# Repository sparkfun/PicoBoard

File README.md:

Picoboard
=========

[ 
*PicoBoard (WIG-10311)*](https://www.sparkfun.com/products/10311)

The PicoBoard allows you to interface hardware sensors with the Scratch programming language.

Repository Contents
-------------------
* **/hardware** - All Eagle design files (.brd, .sch, .STL)
* **/firmware** - PicoBoard source code for an ATmega328.

License Information
-------------------
The contents released under [Creative Commons Share-alike 3.0](http://creativecommons.org/licenses/by-sa/3.0/).

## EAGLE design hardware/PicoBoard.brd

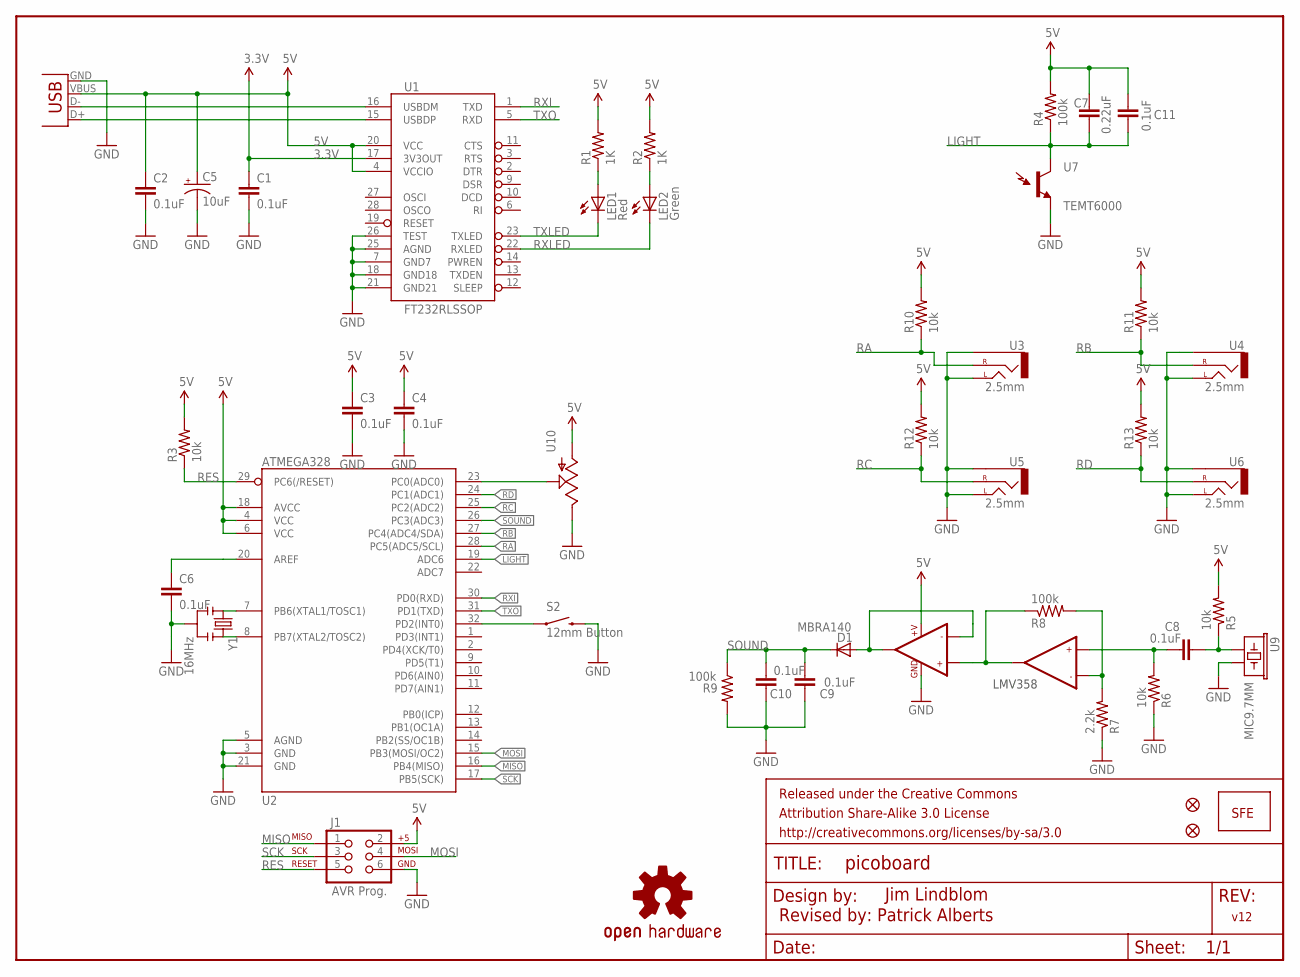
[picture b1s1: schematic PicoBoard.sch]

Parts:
C1, C2, C3, C4, C6, C8, C9, C10, C11: 0.1uF; 0603-CAP
C5: 10uF; EIA3216
C7: 0.22uF; 0603-CAP
D1: MBRA140; SMA-DIODE
FID1, FID2: FIDUCIAL1X2; FIDUCIAL-1X2
FRAME1: FRAME-LETTER; CREATIVE_COMMONS
J1: AVR Prog.; 2X3
JP1: LOGO-SFENEW; SFE-NEW-WEBLOGO
LED1: Red; LED-0603
LED2: Green; LED-0603
LOGO1: OSHW-LOGOL; OSHW-LOGO-L
R1, R2: 1K; 0603-RES
R3, R5, R6, R10, R11, R12, R13: 10k; 0603-RES
R4, R8, R9: 100k; 0603-RES
R7: 2.2k; 0603-RES
S2: 12mm Button; TACTILE-SMD-12MM
U1: FT232RLSSOP; SSOP28DB
U2: ATMEGA328; TQFP32-08
U3, U4, U5, U6: 2.5mm; STEREOJACK2.5MM
U7: TEMT6000; TEMT6000-SEN
U8: LMV358; SO08
U9: MIC9.7MM; MIC-9.7MM
U10: SLIDER60MM; SLIDER
X1: USBSMD; USB-MINIB
Y1: 16MHz; RESONATOR-SMD

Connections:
3.3V: C1.1, U1.17 (3V3OUT)
5V: C2.1, C3.1, C4.1, C5.A (+), C7.1, C11.1, J1.2, R1.2, R2.2, R3.2, R4.2, R5.2, R10.2, R11.2, R12.2, R13.2, U1.4 (VCCIO), U1.20 (VCC), U2.4 (VCC), U2.6 (VCC), U2.18 (AVCC), U8.8 (+V), U10.3 (A), X1.VBUS
GND: C1.2, C2.2, C3.2, C4.2, C5.C (-), C6.2, C9.1, C10.1, J1.6, R6.1, R7.1, R9.2, S2.3 (2), U1.7 (GND7), U1.18 (GND18), U1.21 (GND21), U1.25 (AGND), U1.26 (TEST), U2.3 (GND), U2.5 (AGND), U2.21 (GND), U3.1 (LEFT), U3.5 (SLEEVE), U4.1 (LEFT), U4.5 (SLEEVE), U5.1 (LEFT), U5.5 (SLEEVE), U6.1 (LEFT), U6.5 (SLEEVE), U7.EMITTER (E1), U8.4 (GND), U9.2, U10.1 (E), X1.GND, Y1.2
LIGHT: C7.2, C11.2, R4.1, U2.19 (ADC6), U7.COLLECTOR (C1)
MISO: J1.1, U2.16 (PB4(MISO))
MOSI: J1.4, U2.15 (PB3(MOSI/OC2))
unnamed: LED1.A, R1.1
unnamed: LED2.A, R2.1
unnamed: R7.2, R8.2, U8.6 (-IN2)
unnamed: U2.7 (PB6(XTAL1/TOSC1)), Y1.1
unnamed: U2.8 (PB7(XTAL2/TOSC2)), Y1.3
unnamed: C6.1, U2.20 (AREF)
unnamed: S2.1, U2.32 (PD2(INT0))
unnamed: C8.1, R5.1, U9.1
unnamed: U2.23 (PC0(ADC0)), U10.2A (S)
unnamed: C8.2, R6.2, U8.5 (+IN2)
unnamed: D1.A, U8.1 (OUT1), U8.2 (-IN1)
unnamed: R8.1, U8.3 (+IN1), U8.7 (OUT2)
RA: R10.1, U2.28 (PC5(ADC5/SCL)), U3.4 (RIGHT)
RB: R11.1, U2.27 (PC4(ADC4/SDA)), U4.4 (RIGHT)
RC: R12.1, U2.25 (PC2(ADC2)), U5.4 (RIGHT)
RD: R13.1, U2.24 (PC1(ADC1)), U6.4 (RIGHT)
RES: J1.5, R3.1, U2.29 (PC6(/RESET))
RXI: U1.1 (TXD), U2.30 (PD0(RXD))
RXLED: LED2.C, U1.22 (RXLED)
SCK: J1.3, U2.17 (PB5(SCK))
SOUND: C9.2, C10.2, D1.C, R9.1, U2.26 (PC3(ADC3))
TXLED: LED1.C, U1.23 (TXLED)
TXO: U1.5 (RXD), U2.31 (PD1(TXD))
USB_D+: U1.15 (USBDP), X1.D+
USB_D-: U1.16 (USBDM), X1.D-

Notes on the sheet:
LMV358
Jim Lindblom
Revised by: Patrick Alberts
v12

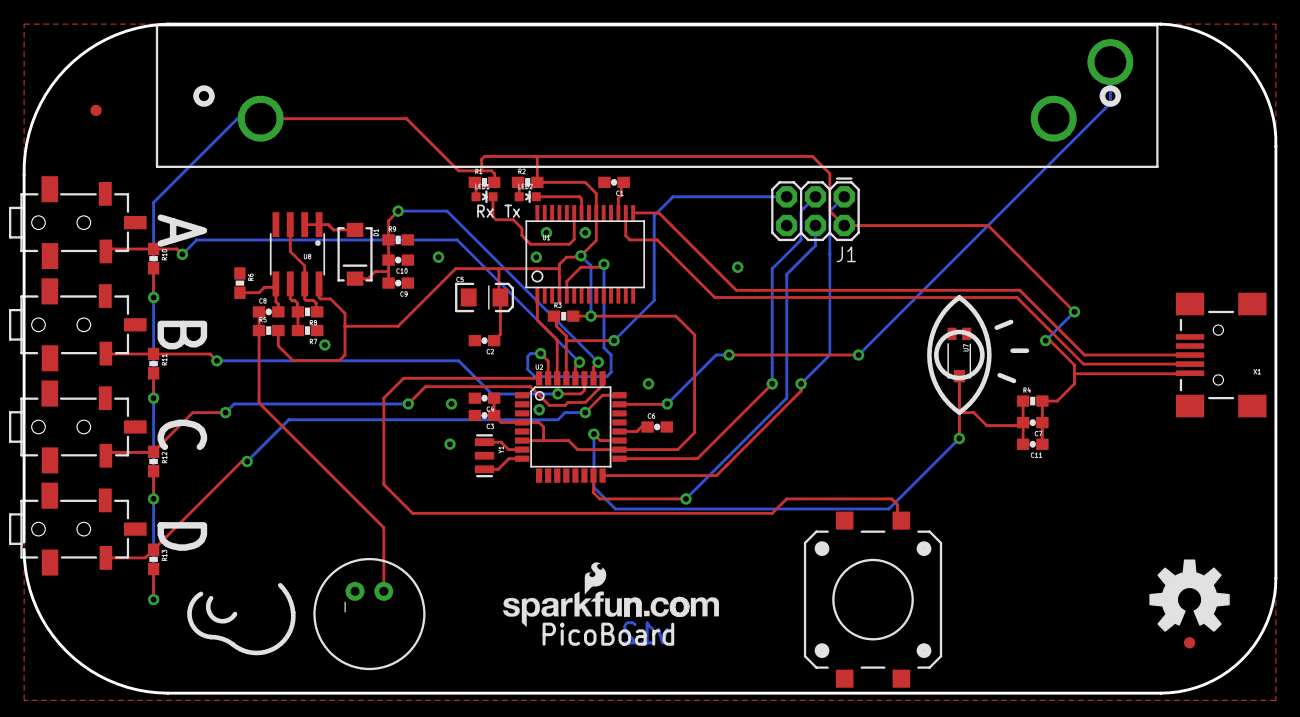
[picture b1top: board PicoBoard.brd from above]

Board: 2 copper layers, 110.5 x 59.1 mm, 46 parts (0 on the bottom side), 31 nets.

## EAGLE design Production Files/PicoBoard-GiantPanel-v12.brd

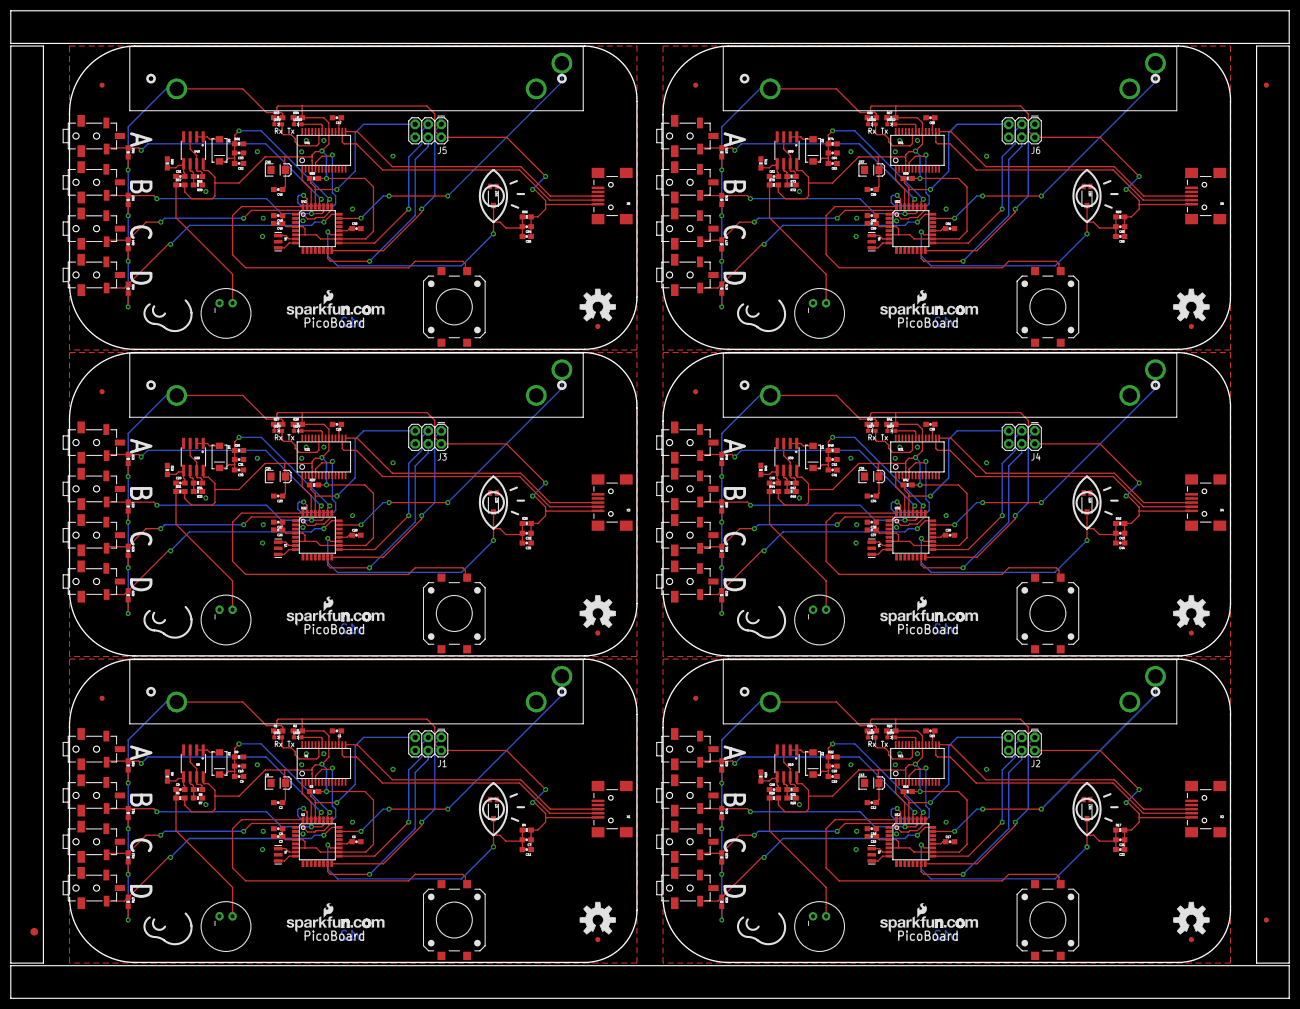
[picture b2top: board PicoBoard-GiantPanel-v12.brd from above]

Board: 2 copper layers, 248.9 x 192.2 mm, 273 parts (0 on the bottom side), 186 nets.

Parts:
C1, C2, C3, C4, C6, C8, C9, C10, C11, C12, C14, C15, C16, C17, C18, C19, C20, C22, C23, C25, C26, C27, C28, C29, C30, C31, C33, C34, C36, C37, C38, C39, C40, C41, C42, C44, C45, C47, C48, C49, C50, C51, C52, C53, C55, C56, C58, C59, C60, C61, C62, C63, C64, C66: 0.1uF; 0603-CAP
C5, C13, C24, C35, C46, C57: 10uF; EIA3216
C7, C21, C32, C43, C54, C65: 0.22uF; 0603-CAP
D1, D2, D3, D4, D5, D6: MBRA140; SMA-DIODE
E$1: FIDUCIAL-1.5X3
E$2, E$4: FIDUCIAL-1X2
FID1, FID2, FID3, FID4, FID5, FID6, FID7, FID8, FID9, FID10, FID11, FID12: FIDUCIAL1X2; FIDUCIAL-1X2
J1, J2, J3, J4, J5, J6: AVR Prog.; 2X3
JP1, JP2, JP3, JP4, JP5, JP6: LOGO-SFENEW; SFE-NEW-WEBLOGO
LED1, LED3, LED5, LED7, LED9, LED11: Red; LED-0603
LED2, LED4, LED6, LED8, LED10, LED12: Green; LED-0603
LOGO1, LOGO2, LOGO3, LOGO4, LOGO5, LOGO6: OSHW-LOGOL; OSHW-LOGO-L
R1, R2, R14, R15, R27, R28, R40, R41, R53, R54, R66, R67: 1K; 0603-RES
R3, R5, R6, R10, R11, R12, R13, R16, R18, R19, R23, R24, R25, R26, R29, R31, R32, R36, R37, R38, R39, R42, R44, R45, R49, R50, R51, R52, R55, R57, R58, R62, R63, R64, R65, R68, R70, R71, R75, R76, R77, R78: 10k; 0603-RES
R4, R8, R9, R17, R21, R22, R30, R34, R35, R43, R47, R48, R56, R60, R61, R69, R73, R74: 100k; 0603-RES
R7, R20, R33, R46, R59, R72: 2.2k; 0603-RES
S1, S2, S3, S4, S5, S6: 12mm Button; TACTILE-SMD-12MM
U1, U11, U21, U31, U41, U51: FT232RLSSOP; SSOP28DB
U2, U12, U22, U32, U42, U52: ATMEGA328; TQFP32-08
U3, U4, U5, U6, U13, U14, U15, U16, U23, U24, U25, U26, U33, U34, U35, U36, U43, U44, U45, U46, U53, U54, U55, U56: 2.5mm; STEREOJACK2.5MM
U7, U17, U27, U37, U47, U57: TEMT6000; TEMT6000-SEN
U8, U19, U29, U39, U49, U59: LMV358; SO08
U9, U18, U28, U38, U48, U58: MIC9.7MM; MIC-9.7MM
U10, U20, U30, U40, U50, U60: SLIDER
X1, X2, X3, X4, X5, X6: USBSMD; USB-MINIB
Y1, Y2, Y3, Y4, Y5, Y6: 16MHz; RESONATOR-SMD

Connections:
3.3V: C1.1, U1.17
3.3V1: C14.1, U11.17
3.3V2: C25.1, U21.17
3.3V3: C36.1, U31.17
3.3V4: C47.1, U41.17
3.3V5: C58.1, U51.17
5V: C2.1, C3.1, C4.1, C5.A, C7.1, C11.1, J1.2, R1.2, R2.2, R3.2, R4.2, R5.2, R10.2, R11.2, R12.2, R13.2, U1.4, U1.20, U2.4, U2.6, U2.18, U8.8, U10.3, X1.VBUS
5V1: C12.1, C13.A, C15.1, C16.1, C21.1, C22.1, J2.2, R14.2, R15.2, R16.2, R17.2, R18.2, R23.2, R24.2, R25.2, R26.2, U11.4, U11.20, U12.4, U12.6, U12.18, U19.8, U20.3, X2.VBUS
5V2: C23.1, C24.A, C26.1, C27.1, C32.1, C33.1, J3.2, R27.2, R28.2, R29.2, R30.2, R31.2, R36.2, R37.2, R38.2, R39.2, U21.4, U21.20, U22.4, U22.6, U22.18, U29.8, U30.3, X3.VBUS
5V3: C34.1, C35.A, C37.1, C38.1, C43.1, C44.1, J4.2, R40.2, R41.2, R42.2, R43.2, R44.2, R49.2, R50.2, R51.2, R52.2, U31.4, U31.20, U32.4, U32.6, U32.18, U39.8, U40.3, X4.VBUS
5V4: C45.1, C46.A, C48.1, C49.1, C54.1, C55.1, J5.2, R53.2, R54.2, R55.2, R56.2, R57.2, R62.2, R63.2, R64.2, R65.2, U41.4, U41.20, U42.4, U42.6, U42.18, U49.8, U50.3, X5.VBUS
5V5: C56.1, C57.A, C59.1, C60.1, C65.1, C66.1, J6.2, R66.2, R67.2, R68.2, R69.2, R70.2, R75.2, R76.2, R77.2, R78.2, U51.4, U51.20, U52.4, U52.6, U52.18, U59.8, U60.3, X6.VBUS
GND: C1.2, C2.2, C3.2, C4.2, C5.C, C6.2, C9.1, C10.1, J1.6, R6.1, R7.1, R9.2, S2.3, U1.7, U1.18, U1.21, U1.25, U1.26, U2.3, U2.5, U2.21, U3.1, U3.5, U4.1, U4.5, U5.1, U5.5, U6.1, U6.5, U7.EMITTER, U8.4, U9.2, U10.1, X1.GND, Y1.2
GND1: C12.2, C13.C, C14.2, C15.2, C16.2, C17.2, C19.1, C20.1, J2.6, R19.1, R20.1, R22.2, S1.3, U11.7, U11.18, U11.21, U11.25, U11.26, U12.3, U12.5, U12.21, U13.1, U13.5, U14.1, U14.5, U15.1, U15.5, U16.1, U16.5, U17.EMITTER, U18.2, U19.4, U20.1, X2.GND, Y2.2
GND2: C23.2, C24.C, C25.2, C26.2, C27.2, C28.2, C30.1, C31.1, J3.6, R32.1, R33.1, R35.2, S3.3, U21.7, U21.18, U21.21, U21.25, U21.26, U22.3, U22.5, U22.21, U23.1, U23.5, U24.1, U24.5, U25.1, U25.5, U26.1, U26.5, U27.EMITTER, U28.2, U29.4, U30.1, X3.GND, Y3.2
GND3: C34.2, C35.C, C36.2, C37.2, C38.2, C39.2, C41.1, C42.1, J4.6, R45.1, R46.1, R48.2, S4.3, U31.7, U31.18, U31.21, U31.25, U31.26, U32.3, U32.5, U32.21, U33.1, U33.5, U34.1, U34.5, U35.1, U35.5, U36.1, U36.5, U37.EMITTER, U38.2, U39.4, U40.1, X4.GND, Y4.2
GND4: C45.2, C46.C, C47.2, C48.2, C49.2, C50.2, C52.1, C53.1, J5.6, R58.1, R59.1, R61.2, S5.3, U41.7, U41.18, U41.21, U41.25, U41.26, U42.3, U42.5, U42.21, U43.1, U43.5, U44.1, U44.5, U45.1, U45.5, U46.1, U46.5, U47.EMITTER, U48.2, U49.4, U50.1, X5.GND, Y5.2
GND5: C56.2, C57.C, C58.2, C59.2, C60.2, C61.2, C63.1, C64.1, J6.6, R71.1, R72.1, R74.2, S6.3, U51.7, U51.18, U51.21, U51.25, U51.26, U52.3, U52.5, U52.21, U53.1, U53.5, U54.1, U54.5, U55.1, U55.5, U56.1, U56.5, U57.EMITTER, U58.2, U59.4, U60.1, X6.GND, Y6.2
LIGHT: C7.2, C11.2, R4.1, U2.19, U7.COLLECTOR
LIGHT1: C21.2, C22.2, R17.1, U12.19, U17.COLLECTOR
LIGHT2: C32.2, C33.2, R30.1, U22.19, U27.COLLECTOR
LIGHT3: C43.2, C44.2, R43.1, U32.19, U37.COLLECTOR
LIGHT4: C54.2, C55.2, R56.1, U42.19, U47.COLLECTOR
LIGHT5: C65.2, C66.2, R69.1, U52.19, U57.COLLECTOR
MISO: J1.1, U2.16
MISO1: J2.1, U12.16
MISO2: J3.1, U22.16
MISO3: J4.1, U32.16
MISO4: J5.1, U42.16
MISO5: J6.1, U52.16
MOSI: J1.4, U2.15
MOSI1: J2.4, U12.15
MOSI2: J3.4, U22.15
MOSI3: J4.4, U32.15
MOSI4: J5.4, U42.15
MOSI5: J6.4, U52.15
unnamed: LED1.A, R1.1
unnamed: LED2.A, R2.1
unnamed: R7.2, R8.2, U8.6
unnamed: LED3.A, R14.1
unnamed: U2.7, Y1.1
unnamed: U2.8, Y1.3
unnamed: C6.1, U2.20
unnamed: S2.1, U2.32
unnamed: C8.1, R5.1, U9.1
unnamed: U2.23, U10.2A
unnamed: C8.2, R6.2, U8.5
unnamed: LED4.A, R15.1
unnamed: D1.A, U8.1, U8.2
unnamed: U12.7, Y2.1
unnamed: U12.8, Y2.3
unnamed: R8.1, U8.3, U8.7
unnamed: C17.1, U12.20
unnamed: S1.1, U12.32
unnamed: C18.1, R18.1, U18.1
unnamed: C18.2, R19.2, U19.5
unnamed: R20.2, R21.2, U19.6
unnamed: D2.A, U19.1, U19.2
unnamed: R21.1, U19.3, U19.7
unnamed: U12.23, U20.2A
unnamed: LED5.A, R27.1
unnamed: LED6.A, R28.1
unnamed: U22.7, Y3.1
unnamed: U22.8, Y3.3
unnamed: C28.1, U22.20
unnamed: S3.1, U22.32
unnamed: C29.1, R31.1, U28.1
unnamed: C29.2, R32.2, U29.5
unnamed: R33.2, R34.2, U29.6
unnamed: D3.A, U29.1, U29.2
unnamed: R34.1, U29.3, U29.7
unnamed: U22.23, U30.2A
unnamed: LED7.A, R40.1
unnamed: LED8.A, R41.1
unnamed: U32.7, Y4.1
unnamed: U32.8, Y4.3
unnamed: C39.1, U32.20
unnamed: S4.1, U32.32
unnamed: C40.1, R44.1, U38.1
unnamed: C40.2, R45.2, U39.5
unnamed: R46.2, R47.2, U39.6
unnamed: D4.A, U39.1, U39.2
unnamed: R47.1, U39.3, U39.7
unnamed: U32.23, U40.2A
unnamed: LED9.A, R53.1
unnamed: LED10.A, R54.1
unnamed: U42.7, Y5.1
unnamed: U42.8, Y5.3
unnamed: C50.1, U42.20
unnamed: S5.1, U42.32
unnamed: C51.1, R57.1, U48.1
unnamed: C51.2, R58.2, U49.5
unnamed: R59.2, R60.2, U49.6
unnamed: D5.A, U49.1, U49.2
unnamed: R60.1, U49.3, U49.7
unnamed: U42.23, U50.2A
unnamed: LED11.A, R66.1
unnamed: LED12.A, R67.1
unnamed: U52.7, Y6.1
unnamed: U52.8, Y6.3
unnamed: C61.1, U52.20
unnamed: S6.1, U52.32
unnamed: C62.1, R70.1, U58.1
unnamed: C62.2, R71.2, U59.5
unnamed: R72.2, R73.2, U59.6
unnamed: D6.A, U59.1, U59.2
unnamed: R73.1, U59.3, U59.7
unnamed: U52.23, U60.2A
RA: R10.1, U2.28, U3.4
RA1: R23.1, U12.28, U13.4
RA2: R36.1, U22.28, U23.4
RA3: R49.1, U32.28, U33.4
RA4: R62.1, U42.28, U43.4
RA5: R75.1, U52.28, U53.4
RB: R11.1, U2.27, U4.4
RB1: R24.1, U12.27, U14.4
RB2: R37.1, U22.27, U24.4
RB3: R50.1, U32.27, U34.4
RB4: R63.1, U42.27, U44.4
RB5: R76.1, U52.27, U54.4
RC: R12.1, U2.25, U5.4
RC1: R25.1, U12.25, U15.4
RC2: R38.1, U22.25, U25.4
RC3: R51.1, U32.25, U35.4
RC4: R64.1, U42.25, U45.4
RC5: R77.1, U52.25, U55.4
RD: R13.1, U2.24, U6.4
RD1: R26.1, U12.24, U16.4
RD2: R39.1, U22.24, U26.4
RD3: R52.1, U32.24, U36.4
RD4: R65.1, U42.24, U46.4
RD5: R78.1, U52.24, U56.4
RES: J1.5, R3.1, U2.29
RES1: J2.5, R16.1, U12.29
RES2: J3.5, R29.1, U22.29
RES3: J4.5, R42.1, U32.29
RES4: J5.5, R55.1, U42.29
RES5: J6.5, R68.1, U52.29
RXI: U1.1, U2.30
RXI1: U11.1, U12.30
RXI2: U21.1, U22.30
RXI3: U31.1, U32.30
RXI4: U41.1, U42.30
RXI5: U51.1, U52.30
RXLED: LED2.C, U1.22
RXLED1: LED4.C, U11.22
RXLED2: LED6.C, U21.22
RXLED3: LED8.C, U31.22
RXLED4: LED10.C, U41.22
RXLED5: LED12.C, U51.22
SCK: J1.3, U2.17
SCK1: J2.3, U12.17
SCK2: J3.3, U22.17
SCK3: J4.3, U32.17
SCK4: J5.3, U42.17
SCK5: J6.3, U52.17
SOUND: C9.2, C10.2, D1.C, R9.1, U2.26
SOUND1: C19.2, C20.2, D2.C, R22.1, U12.26
SOUND2: C30.2, C31.2, D3.C, R35.1, U22.26
SOUND3: C41.2, C42.2, D4.C, R48.1, U32.26
SOUND4: C52.2, C53.2, D5.C, R61.1, U42.26
SOUND5: C63.2, C64.2, D6.C, R74.1, U52.26
TXLED: LED1.C, U1.23
TXLED1: LED3.C, U11.23
TXLED2: LED5.C, U21.23
TXLED3: LED7.C, U31.23
TXLED4: LED9.C, U41.23
TXLED5: LED11.C, U51.23
TXO: U1.5, U2.31
TXO1: U11.5, U12.31
TXO2: U21.5, U22.31
TXO3: U31.5, U32.31
TXO4: U41.5, U42.31
TXO5: U51.5, U52.31
USB_D+: U1.15, X1.D+
USB_D+1: U11.15, X2.D+
USB_D+2: U21.15, X3.D+
USB_D+3: U31.15, X4.D+
USB_D+4: U41.15, X5.D+
USB_D+5: U51.15, X6.D+
USB_D-: U1.16, X1.D-
USB_D-1: U11.16, X2.D-
USB_D-2: U21.16, X3.D-
USB_D-3: U31.16, X4.D-
USB_D-4: U41.16, X5.D-
USB_D-5: U51.16, X6.D-

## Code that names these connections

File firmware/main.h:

//*******************************************************
//					GPIO Definitions
#define SLIDER PINC0
#define RD	PINC1
#define RC	PINC2
#define SOUND	PINC3
#define RB	PINC4
#define RA	PINC5
#define LIGHT	PINC6

#define RXI	PIND0
#define TXO	PIND1
#define BUTTON PIND2


//*******************************************************
//						Macros
//*******************************************************
#define sbi(var, mask)   ((var) |= (uint8_t)(1 << mask))
#define cbi(var, mask)   ((var) &= (uint8_t)~(1 << mask))


//*******************************************************
//					General Definitions
//*******************************************************
#define MYUBRR 51	//Used to set the AVR Baud Rate TO 38400 (External 16MHz Oscillator)

#define SCRATCH_DATA_REQUEST	0x01
#define SCRATCH_FW_VER			0x04

//=======================================================
//					Function Definitions
//=======================================================
static int uart_putchar(char c, FILE *stream);
uint8_t uart_getchar(void);
static FILE mystdout = FDEV_SETUP_STREAM(uart_putchar, NULL, _FDEV_SETUP_WRITE);
void ioinit(void);
void delay_ms(uint16_t x);
void delay_us(uint16_t x);
void buildScratchPacket(char * packet, int channel, int value);
void sendScratchPacket(char * packet);

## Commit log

2013-09-23 Initial BRD/SCH file commit
    added board and schematic files with gitignore
2013-10-11 0603 Changed, Schematic Changes
    Changed all caps and res to 0603 and re routed accordingly as well as
    added OSHW logo and cleaned up the schematice
2013-11-09 Adding firmware to repo
2013-11-09 Removing extra firmware files.
2013-11-09 Removing dependencies
2013-11-11 Cleaning up readme.
2013-12-06 Stereo Jack 1:1 updated
2013-12-16 Trace clean up
2014-02-20 Re-Up
    The New REV somehow was lost, now it is not.
2014-03-04 Re- Up
    95% of the orginal Rev files we're lost, updated the lost files.
2014-03-05 Added board fiducials
2014-03-06 Created giant panel v12
2025-06-27 Update README.md
    Updating link

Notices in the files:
parts and their libraries:
SparkFun-Aesthetics: Licensing: CC v3.0 Share-Alike You are welcome to use this library for commercial purposes.
SparkFun-Electromechanical: Licensing: Creative Commons ShareAlike 4.0 International - https://creativecommons.org/licenses/by-sa/4.0
